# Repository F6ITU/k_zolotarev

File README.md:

# Zolotarev Low Pass Filter

This lpf filter has been described by Gary Cobb, G3TMG, in QEX (November-December 2016). 

Based on this model, Kjell LA2NI designed a complete low-pass filter, capable of handling (at least) 600W of RF power. 

It's the ideal companion for the Munin400 linear amplifier designed by the same author.

This repository is a strict copy of the original work, using Kicad 8.xx. Original pcb design was made with Ultiboard software

# Building notes : 

** All capacitors used in the active part of the filter have been sourced as "Vishay Vitramon VJ Hifreq" in 1111 format./**

For   safety reasons and voltage/power handling, the operating voltage of each capacitor should not be less than 1kV.

In other words, since the voltage withstand of MLCC capacitors (or any other technology) decreases as the capacitance increases, the maximum value of each component must not exceed 180 pF (beyond this value, the voltage withstand
resistance collapses at 630 V).

This is why parallel capacitor associations have been provided on the pcb (referenced with the suffix Cxxb1, Cxxb2 etc).

** Two kind of output are available.

- One on SMA connectors

- The other by soldering a coaxial cable directly to the pcb (pigtail input/output)

The second method is preferable, as it's more practical for many hobbyists. However, at these frequencies (1 to 60 MHz), SMA connectors support these power levels perfectly. Avoid connectors made in China.

Input and output wiring on 5mm coax such as RG233 or equivalent (or hand formable SM141 coax cable if SMA are used).

Toroid should be wound with 6 to 8 tenths of a mm wire, air-cores with 8/10 silver-plated wire.

# Work in progress ?

The current state of the filter is considered as "RTM", Beta 1, and considered as "almost definitive" for a first version.

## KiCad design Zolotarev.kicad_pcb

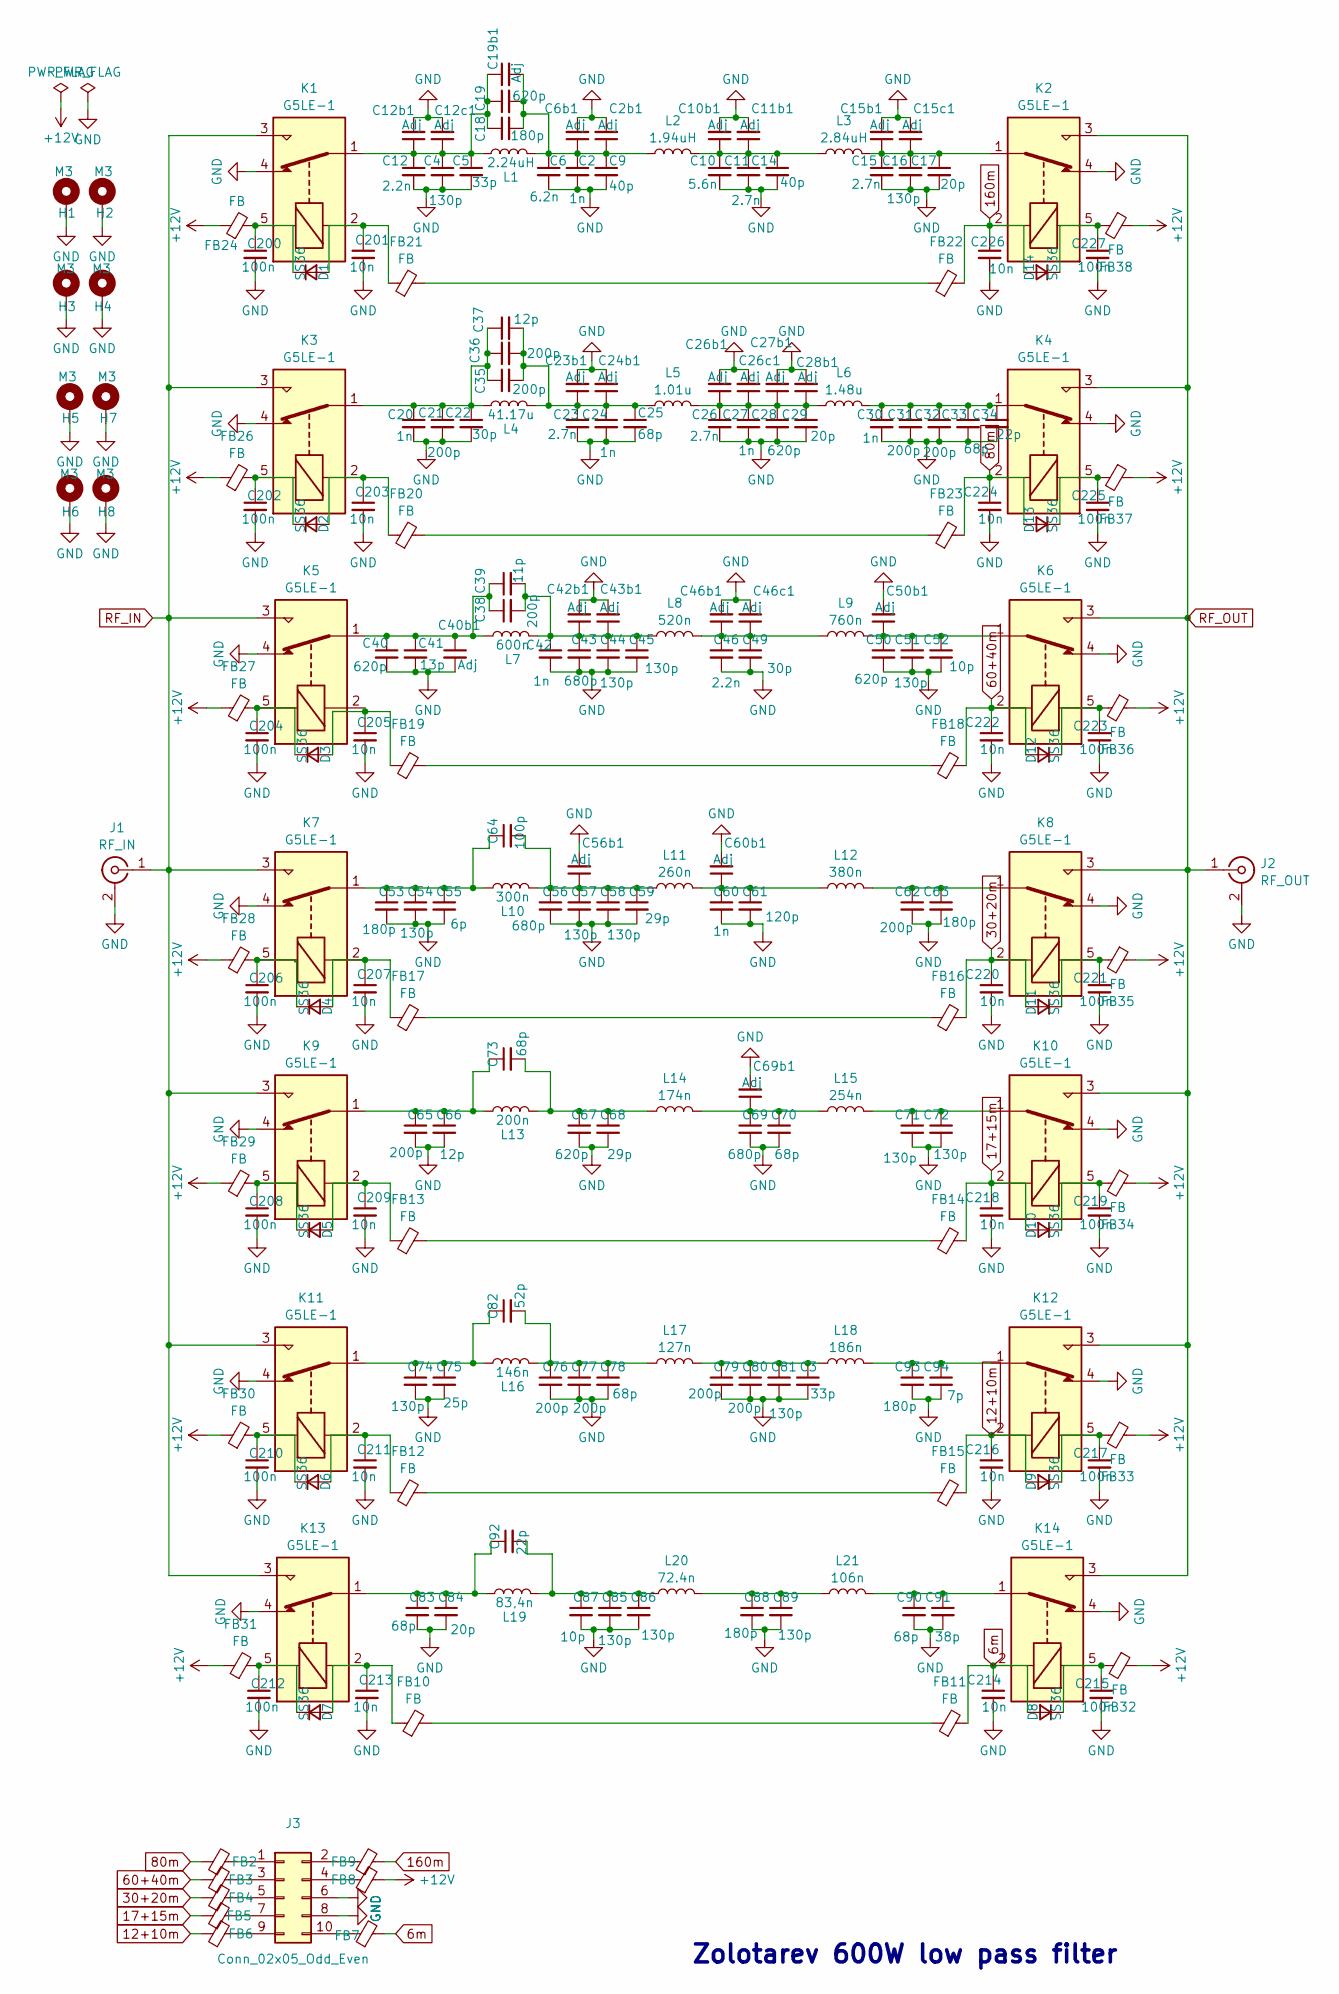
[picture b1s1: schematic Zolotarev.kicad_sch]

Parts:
C2, C20, C24, C27, C30, C42, C60: 1n; ATC_500_HandSoldering
C2b1, C6b1, C10b1, C11b1, C12b1, C12c1, C15b1, C15c1, C19b1, C23b1, C24b1, C26b1, C26c1, C27b1, C28b1, C40b1, C42b1, C43b1, C46b1, C46c1, C50b1, C56b1, C60b1, C69b1: Adj; ATC_500_HandSoldering
C3, C5: 33p; ATC_500_HandSoldering
C4, C16, C44, C45, C51, C54, C57, C58, C71, C72, C74, C81, C85, C86, C89: 130p; ATC_500_HandSoldering
C6: 6.2n; ATC_500_HandSoldering
C9, C14: 40p; ATC_500_HandSoldering
C10: 5.6n; ATC_500_HandSoldering
C11, C15, C23, C26: 2.7n; ATC_500_HandSoldering
C12, C46: 2.2n; ATC_500_HandSoldering
C17, C29, C84: 20p; ATC_500_HandSoldering
C18, C53, C63, C88, C93: 180p; ATC_500_HandSoldering
C19, C28, C40, C50, C67: 620p; ATC_500_HandSoldering
C21, C31, C32, C35, C36, C38, C62, C65, C76, C77, C79, C80: 200p; ATC_500_HandSoldering
C22, C49: 30p; ATC_500_HandSoldering
C25, C33, C70, C73, C78, C83, C90: 68p; ATC_500_HandSoldering
C34, C92: 22p; ATC_500_HandSoldering
C37, C66: 12p; ATC_500_HandSoldering
C39: 11p; ATC_500_HandSoldering
C41: 13p; ATC_500_HandSoldering
C43, C56, C69: 680p; ATC_500_HandSoldering
C52, C87: 10p; ATC_500_HandSoldering
C55: 6p; ATC_500_HandSoldering
C59, C68: 29p; ATC_500_HandSoldering
C61: 120p; ATC_500_HandSoldering
C64: 100p; ATC_500_HandSoldering
C75: 25p; ATC_500_HandSoldering
C82: 52p; ATC_500_HandSoldering
C91: 38p; ATC_500_HandSoldering
C94: 7p; ATC_500_HandSoldering
C200, C202, C204, C206, C208, C210, C212, C215, C217, C219, C221, C223, C225, C227: 100n; C_0805_2012Metric_Pad1.18x1.45mm_HandSolder
C201, C203, C205, C207, C209, C211, C213, C214, C216, C218, C220, C222, C224, C226: 10n; C_0805_2012Metric_Pad1.18x1.45mm_HandSolder
D1, D2, D3, D4, D5, D6, D7, D8, D9, D10, D11, D12, D13, D14: SS36; D_SMB_Handsoldering
FB2, FB3, FB4, FB5, FB6, FB7, FB8, FB9, FB10, FB11, FB12, FB13, FB14, FB15, FB16, FB17, FB18, FB19, FB20, FB21, FB22, FB23, FB24, FB26, FB27, FB28, FB29, FB30, FB31, FB32, FB33, FB34, FB35, FB36, FB37, FB38: FB; L_0805_2012Metric_Pad1.15x1.40mm_HandSolder
H1, H2, H3, H4, H5, H6, H7, H8: M3; MountingHole_3.5mm_Pad_Via
J1: RF_IN; SMA_PINS
J2: RF_OUT; SMA_PINS
J3: Conn_02x05_Odd_Even; IDC-Header_2x05_P2.54mm_Vertical
K1, K2, K3, K4, K5, K6, K7, K8, K9, K10, K11, K12, K13, K14: G5LE-1; Relay_SPDT_Omron-G5LE-1
L1: 2.24uH; T90_60_V
L2: 1.94uH; T90_60_V
L3: 2.84uH; T90_60_V
L4: 41.17u; T90_60_V
L5: 1.01u; T90_60_V
L6: 1.48u; T90_60_V
L7: 600n; T90_60_V
L8: 520n; T90_60_V
L9: 760n; T90_60_V
L10: 300n; T90_60_V
L11: 260n; T90_60_V
L12: 380n; T90_60_V
L13: 200n; T90_60_V
L14: 174n; T90_60_V
L15: 254n; T90_60_V
L16: 146n; Large_Air_Coil
L17: 127n; Large_Air_Coil
L18: 186n; Large_Air_Coil
L19: 83,4n; Large_Air_Coil
L20: 72.4n; Large_Air_Coil
L21: 106n; Large_Air_Coil

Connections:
6m: C214.1, D8.2 (A), FB7.2, FB11.2, K14.2
12+10m: C216.1, D9.2 (A), FB6.1, FB15.2, K12.2
17+15m: C218.1, D10.2 (A), FB5.1, FB14.2, K10.2
30+20m: C220.1, D11.2 (A), FB4.1, FB16.2, K8.2
60+40m: C222.1, D12.2 (A), FB3.1, FB18.2, K6.2
80m: C224.1, D13.2 (A), FB2.1, FB23.2, K4.2
160m: C226.1, D14.2 (A), FB9.2, FB22.2, K2.2
+12V: FB8.2, FB24.1, FB26.1, FB27.1, FB28.1, FB29.1, FB30.1, FB31.1, FB32.1, FB33.1, FB34.1, FB35.1, FB36.1, FB37.1, FB38.1
GND: C2.2, C2b1.2, C3.2, C4.2, C5.2, C6.2, C6b1.2, C9.2, C10.2, C10b1.2, C11.2, C11b1.2, C12.2, C12b1.2, C12c1.2, C14.2, C15.2, C15b1.2, C15c1.2, C16.2, C17.2, C20.2, C21.2, C22.2, C23.2, C23b1.2, C24.2, C24b1.2, C25.2, C26.2, C26b1.2, C26c1.2, C27.2, C27b1.2, C28.2, C28b1.2, C29.2, C30.2, C31.2, C32.2, C33.2, C34.2, C40.2, C40b1.2, C41.2, C42.2, C42b1.2, C43.2, C43b1.2, C44.2, C45.2, C46.2, C46b1.2, C46c1.2, C49.2, C50.2, C50b1.2, C51.2, C52.2, C53.2, C54.2, C55.2, C56.2, C56b1.2, C57.2, C58.2, C59.2, C60.2, C60b1.2, C61.2, C62.2, C63.2, C65.2, C66.2, C67.2, C68.2, C69.2, C69b1.2, C70.2, C71.2, C72.2, C74.2, C75.2, C76.2, C77.2, C78.2, C79.2, C80.2, C81.2, C83.2, C84.2, C85.2, C86.2, C87.2, C88.2, C89.2, C90.2, C91.2, C93.2, C94.2, C200.2, C201.2, C202.2, C203.2, C204.2, C205.2, C206.2, C207.2, C208.2, C209.2, C210.2, C211.2, C212.2, C213.2, C214.2, C215.2, C216.2, C217.2, C218.2, C219.2, C220.2, C221.2, C222.2, C223.2, C224.2, C225.2, C226.2, C227.2, H1.1, H2.1, H3.1, H4.1, H5.1, H6.1, H7.1, H8.1, J1.2 (Ext), J2.2 (Ext), J3.6, J3.8, K1.4, K2.4, K3.4, K4.4, K5.4, K6.4, K7.4, K8.4, K9.4, K10.4, K11.4, K12.4, K13.4, K14.4
unnamed: C3.1, C79.1, C80.1, C81.1, L17.2, L18.2
unnamed: C10.1, C10b1.1, C11.1, C11b1.1, C14.1, L2.2, L3.2
unnamed: C4.1, C5.1, C12.1, C12b1.1, C12c1.1, C18.1, C19.1, C19b1.1, K1.1, L1.1
unnamed: C15.1, C15b1.1, C15c1.1, C16.1, C17.1, K2.1, L3.1
unnamed: C2.1, C2b1.1, C6.1, C6b1.1, C9.1, C18.2, C19.2, C19b1.2, L1.2, L2.1
unnamed: C20.1, C21.1, C22.1, C35.1, C36.1, C37.1, K3.1, L4.1
unnamed: C23.1, C23b1.1, C24.1, C24b1.1, C25.1, C35.2, C36.2, C37.2, L4.2, L5.1
unnamed: C26.1, C26b1.1, C26c1.1, C27.1, C27b1.1, C28.1, C28b1.1, C29.1, L5.2, L6.2
unnamed: C30.1, C31.1, C32.1, C33.1, C34.1, K4.1, L6.1
unnamed: C38.1, C39.1, C40.1, C40b1.1, C41.1, K5.1, L7.1
unnamed: C38.2, C39.2, C42.1, C42b1.1, C43.1, C43b1.1, C44.1, C45.1, L7.2, L8.1
unnamed: C46.1, C46b1.1, C46c1.1, C49.1, L8.2, L9.2
unnamed: C50.1, C50b1.1, C51.1, C52.1, K6.1, L9.1
unnamed: C53.1, C54.1, C55.1, C64.1, K7.1, L10.1
unnamed: C56.1, C56b1.1, C57.1, C58.1, C59.1, C64.2, L10.2, L11.1
unnamed: C60.1, C60b1.1, C61.1, L11.2, L12.2
unnamed: C62.1, C63.1, K8.1, L12.1
unnamed: C65.1, C66.1, C73.1, K9.1, L13.1
unnamed: C67.1, C68.1, C73.2, L13.2, L14.1
unnamed: C69.1, C69b1.1, C70.1, L14.2, L15.2
unnamed: C71.1, C72.1, K10.1, L15.1
unnamed: C74.1, C75.1, C82.1, K11.1, L16.1
unnamed: C76.1, C77.1, C78.1, C82.2, L16.2, L17.1
unnamed: C83.1, C84.1, C92.1, K13.1, L19.1
unnamed: C85.1, C86.1, C87.1, C92.2, L19.2, L20.1
unnamed: C88.1, C89.1, L20.2, L21.2
unnamed: C90.1, C91.1, K14.1, L21.1
unnamed: C93.1, C94.1, K12.1, L18.1
unnamed: C201.1, D1.2 (A), FB21.1, K1.2
unnamed: C200.1, D1.1 (K), FB24.2, K1.5
unnamed: C203.1, D2.2 (A), FB20.1, K3.2
unnamed: C202.1, D2.1 (K), FB26.2, K3.5
unnamed: C205.1, D3.2 (A), FB19.1, K5.2
unnamed: C204.1, D3.1 (K), FB27.2, K5.5
unnamed: C207.1, D4.2 (A), FB17.1, K7.2
unnamed: C206.1, D4.1 (K), FB28.2, K7.5
unnamed: C209.1, D5.2 (A), FB13.1, K9.2
unnamed: C208.1, D5.1 (K), FB29.2, K9.5
unnamed: C211.1, D6.2 (A), FB12.1, K11.2
unnamed: C210.1, D6.1 (K), FB30.2, K11.5
unnamed: C213.1, D7.2 (A), FB10.1, K13.2
unnamed: C212.1, D7.1 (K), FB31.2, K13.5
unnamed: C215.1, D8.1 (K), FB32.2, K14.5
unnamed: C217.1, D9.1 (K), FB33.2, K12.5
unnamed: C219.1, D10.1 (K), FB34.2, K10.5
unnamed: C221.1, D11.1 (K), FB35.2, K8.5
unnamed: C223.1, D12.1 (K), FB36.2, K6.5
unnamed: C225.1, D13.1 (K), FB37.2, K4.5
unnamed: C227.1, D14.1 (K), FB38.2, K2.5
unnamed: FB10.2, FB11.1
unnamed: FB12.2, FB15.1
unnamed: FB13.2, FB14.1
unnamed: FB16.1, FB17.2
unnamed: FB18.1, FB19.2
unnamed: FB20.2, FB23.1
unnamed: FB21.2, FB22.1
unnamed: FB2.2, J3.1
unnamed: FB9.1, J3.2
unnamed: FB3.2, J3.3
unnamed: FB8.1, J3.4
unnamed: FB4.2, J3.5
unnamed: FB5.2, J3.7
unnamed: FB6.2, J3.9
unnamed: FB7.1, J3.10
RF_IN: J1.1 (In), K1.3, K3.3, K5.3, K7.3, K9.3, K11.3, K13.3
RF_OUT: J2.1 (In), K2.3, K4.3, K6.3, K8.3, K10.3, K12.3, K14.3

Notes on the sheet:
Zolotarev 600W low pass filter

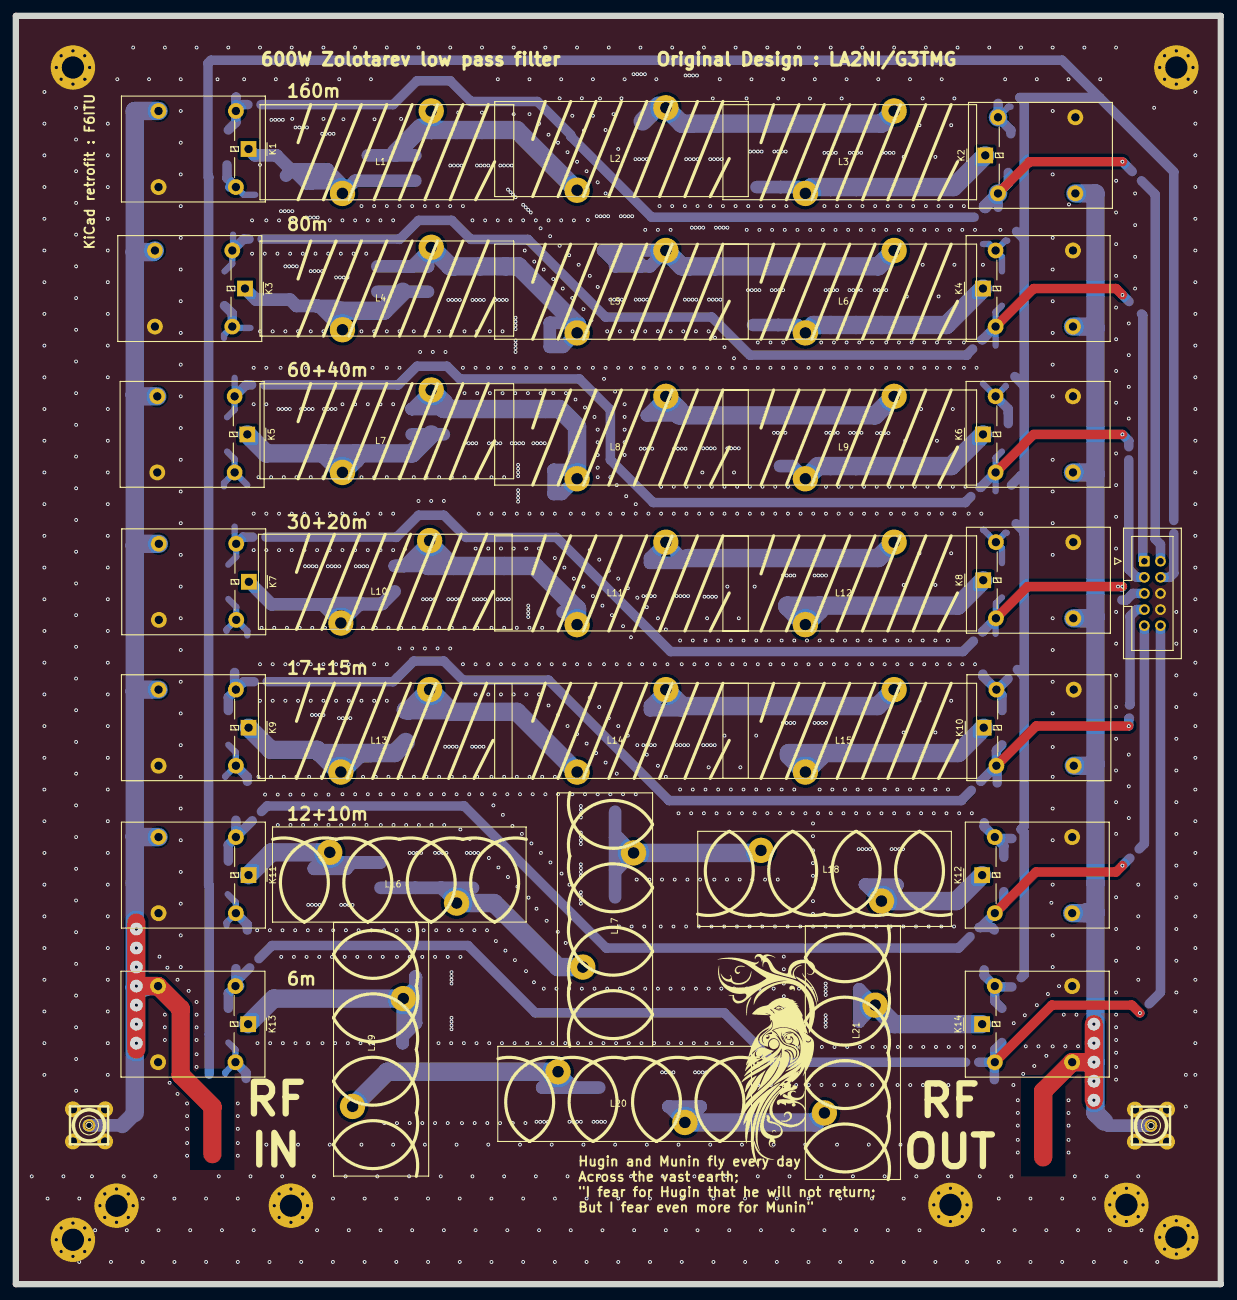
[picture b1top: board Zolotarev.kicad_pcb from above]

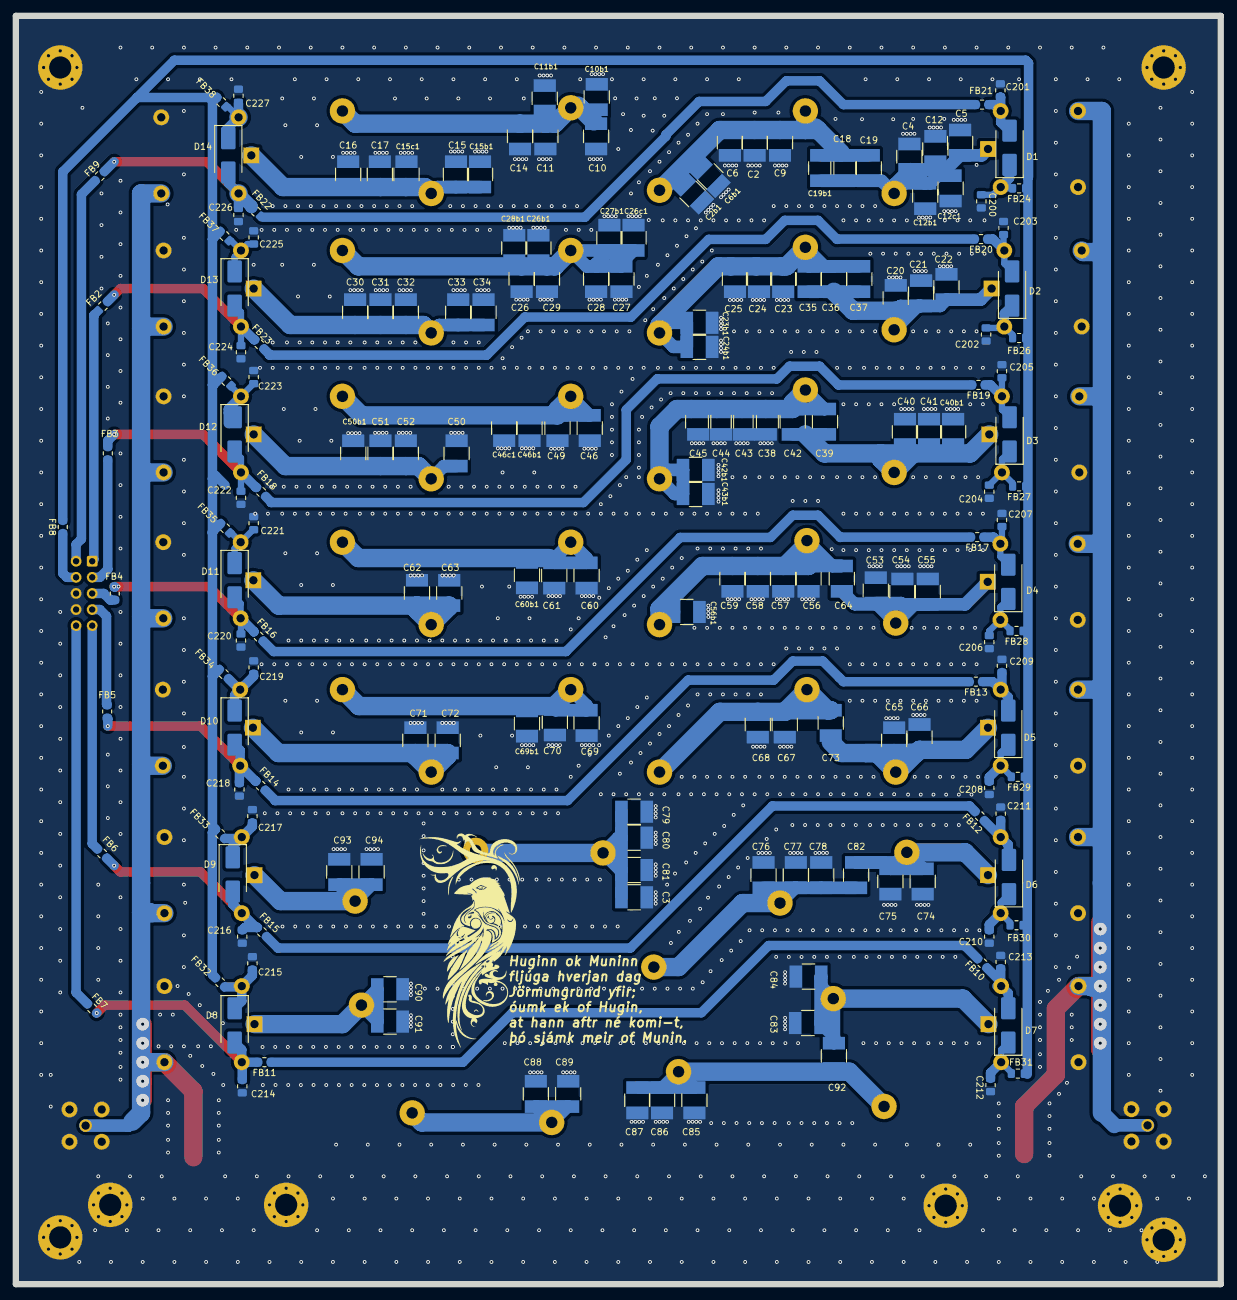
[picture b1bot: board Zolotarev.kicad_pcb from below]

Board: 2 copper layers, 190.0 x 200.0 mm, 236 parts (190 on the bottom side), 75 nets.

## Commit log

2024-11-03 initial project, schematic under dev
2024-11-04 schematic completed, devices def TBD
2024-11-06 beginning to assign 3D forms
2024-11-07 minor corrections, first band routed
2024-11-08 3 bands over 7
2024-11-08 5 bands routed, 2 more to come
2024-11-09 all bands routed, command connector to do
2024-11-09 silkmask partly added
2024-11-10 diodes changed for smb, silk cleaned
2024-11-11 control connector and some ferrites later
2024-11-18 routing, silk, zone cleanup and Gerber completed, RTM release
2024-11-18 new readme and pictures
